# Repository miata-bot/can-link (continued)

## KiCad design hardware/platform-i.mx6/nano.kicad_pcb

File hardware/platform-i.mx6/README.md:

# I.MX6 Platform Board

This is where the functioning I.MX6 board will go when it's done.
Currently in production at PCBWay, assuming the devboard works, this project will get reworked into the correct form factor for the Platform board. It's already the correct width, just needs tidying and connectors.

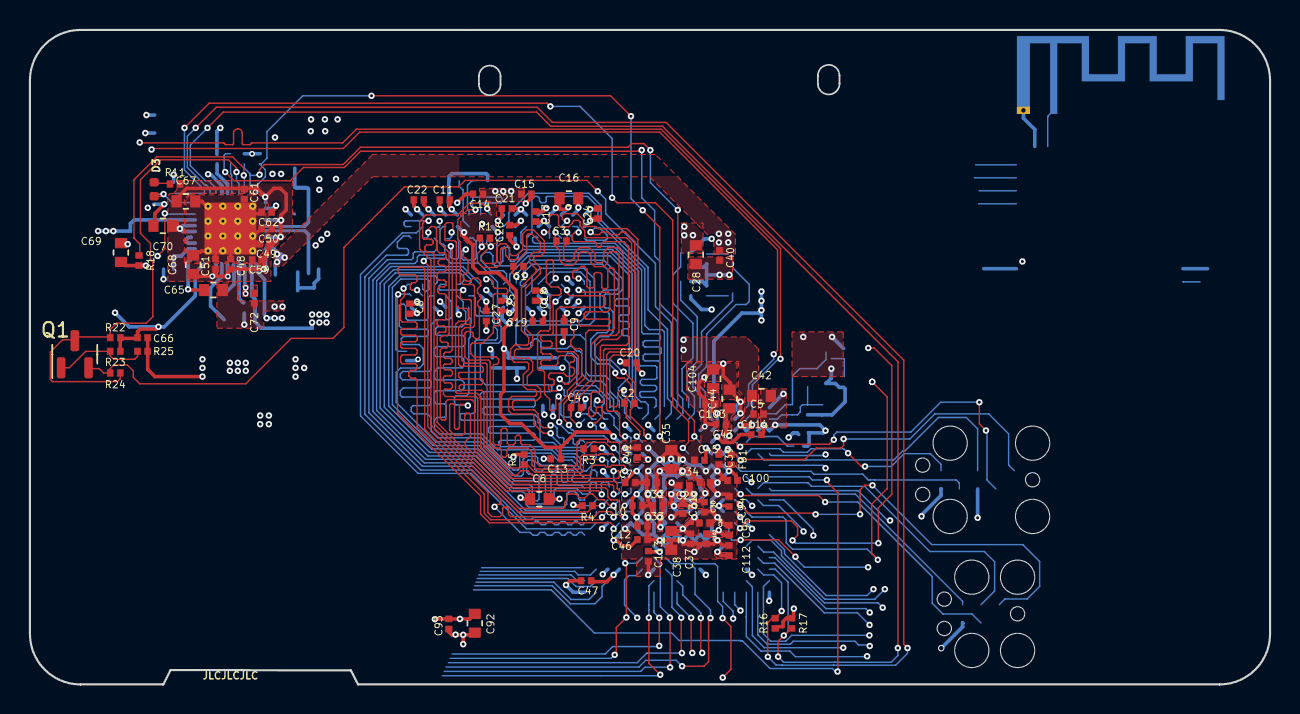
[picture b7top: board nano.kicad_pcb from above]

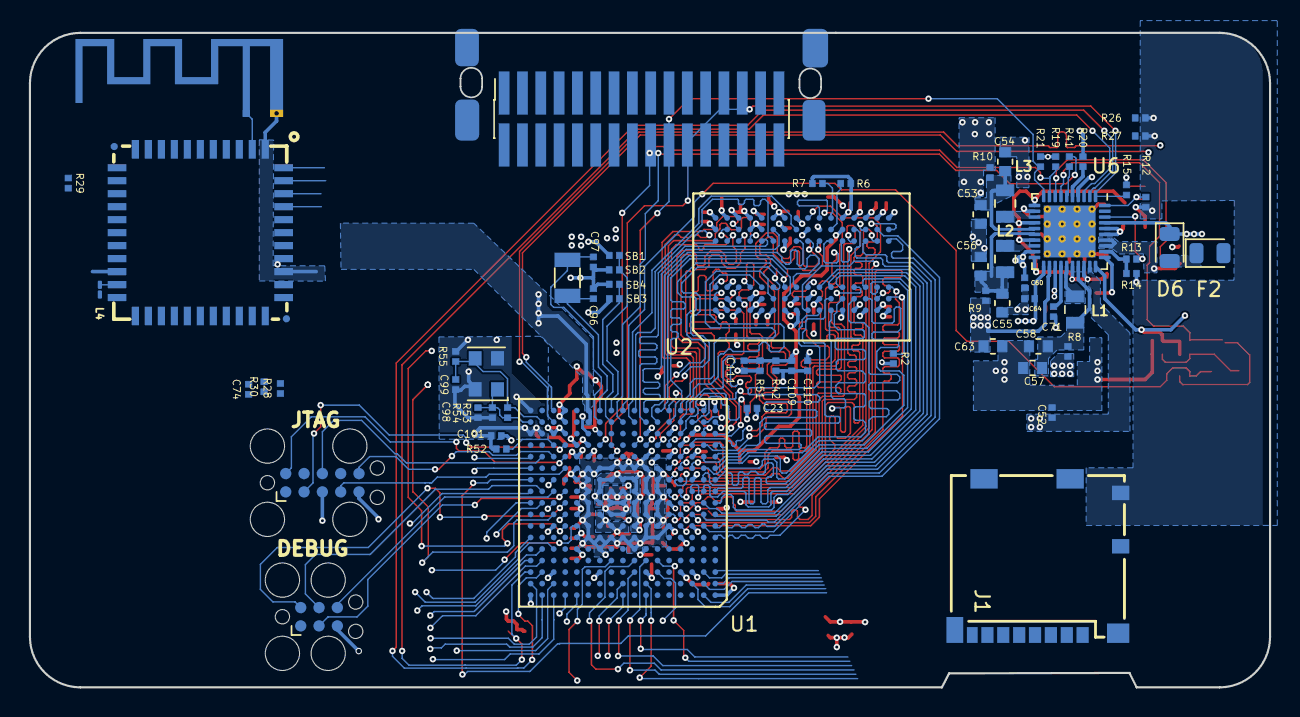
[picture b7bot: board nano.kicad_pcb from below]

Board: 4 copper layers, 86.0 x 45.4 mm, 153 parts (67 on the bottom side), 141 nets.

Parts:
ANT1: PCB_ANTENNA; Texas_SWRA117D_2.4GHz_Left
C1, C2, C3, C4: 2.2pF; C_0402_narrow
C5, C7, C8, C9, C10, C11, C12, C13, C14, C15, C17, C18, C19, C20, C21, C22, C23, C24, C25, C26, C27, C30, C31, C32, C33, C34, C36, C37, C40, C41, C43, C45, C46, C47, C94, C95, C102, C114: 0.22uF; C_0402_narrow
C6, C42, C44, C53, C54, C55, C56, C57, C58, C104: 10uF; C_0603_narrow
C16, C28, C35, C38, C92: 22uF; C_0603_narrow
C29, C39, C48, C49, C50, C52, C60, C62, C110: 4.7uF; C_0402_narrow
C51, C59, C61, C64, C71, C72, C101: 1uF; C_0402_narrow
C63: 1uF; C_0603_narrow
C65: 0.1uF; C_0603_narrow
C66: 0.47uF; C_0402_narrow
C67, C68: 100uF; C_0603_narrow
C69, C70: 4.7uF; C_0603_narrow
C74: 4.7F; C_0402_narrow
C93, C100, C103, C109, C111, C112, C113: 0.1uF; C_0402_narrow
C96, C97, C98, C99: 18pF; C_0402_narrow
D3: LED; LED_0402_1005Metric
D6: D_Schottky; D_0805_2012Metric
F2: Polyfuse; D_0805_2012Metric
FB1: Bead; R_0402_narrow
J1: SD-104031; uSD_104031
J2: TAG_CONNECT_JTAG; Tag-Connect_TC2050-IDC-FP_2x05_P1.27mm_Vertical
J2#2: Conn_02x15_Odd_Even_Shielded; PinSocket_2x16_P1.27mm_Vertical_SMD
J3: TC2030-IDC; Tag-Connect_TC2030-IDC-FP_2x03_P1.27mm_Vertical
L1, L2, L3: 1uH; L_0805_narrow
L4: 3.3uH; L_01005_0402Metric_Pad0.57x0.30mm_HandSolder
MOD1: RTL8723BS; RL-SM02BD(RTL8723BS)
Q1: 2SK3018; SOT-23
R1: 470; R_0402_narrow
R2, R4, R5: 10K; R_0402_narrow
R3, R6, R7: 240; R_0402_narrow
R8, R9, R10: 0.02; R_0402_narrow
R11: 47; R_0402_narrow
R12, R14, R24: DNP; R_0402_narrow
R13, R16, R17, R52: 4.7K; R_0402_narrow
R15, R18, R19, R21, R22, R23, R25: 100K; R_0402_narrow
R20, R41: 0R; R_0402_narrow
R26, R27: 5.1k; R_0402_narrow
R28, R29: 1k; R_0402_narrow
R30: 7.13; R_0402_narrow
R42, R51: 1.5K; R_0402_narrow
R53: 1M; R_0402_narrow
R54: 499; R_0402_narrow
R55: 2.2M; R_0402_narrow
SB1, SB2, SB3, SB4: 4.7K; R_0402_narrow
U1: IMX6UL_BGA289
U2: DDR3_BGA96
U6: PF1550; QFN-40-1EP_5x5mm_P0.4mm_EP3.6x3.6mm_ThermalVias
XTAL2: 24MHz 50ppm; Oscillator_SMD_EuroQuartz_XO32-4Pin_3.2x2.5mm
Y1: 32.768 kHz; Crystal_SMD_3215-2Pin_3.2x1.5mm

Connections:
5V: D6.1 (K), U1.T12 (USB_OTG1_VBUS), U1.U12 (USB_OTG2_VBUS), U6.37 (VBUSIN(VIN))
/Clock_and_Control/BOOT0: SB3.1, SB4.1, U1.T10 (BOOT_MODE0)
/Clock_and_Control/BOOT1: SB1.1, SB2.1, U1.U10 (BOOT_MODE1)
/Clock_and_Control/IMX_XTALI: C99.1, R53.1, R55.1, U1.T16 (XTALI), XTAL2.3
/Clock_and_Control/IMX_XTALO: C98.1, R53.2, R54.1, U1.T17 (XTALO), XTAL2.1
/Clock_and_Control/JTAG_MOD: R52.2, U1.P15 (JTAG_MOD)
/Clock_and_Control/JTAG_TCK: J2.4 (SWDCLK/TCK), U1.M14 (JTAG_TCK)
/Clock_and_Control/JTAG_TDI: J2.8 (NC/TDI), U1.N16 (JTAG_TDI)
/Clock_and_Control/JTAG_TDO: J2.6 (SWO/TDO), U1.N15 (JTAG_TDO)
/Clock_and_Control/JTAG_TMS: J2.2 (SWDIO/TMS), U1.P14 (JTAG_TMS)
/Clock_and_Control/JTAG_TRST_B: J2.10 (~RESET), U1.N14 (JTAG_TRST_B)
/Clock_and_Control/RTC_XTALI: C97.1, U1.T11 (RTC_XTALI), Y1.2
/Clock_and_Control/RTC_XTALO: C96.1, U1.U11 (RTC_XTALO), Y1.1
/Clock_and_Control/VDDA_ADC: C100.1, C101.1, FB1.2, U1.L13 (VDDA_ADC_3P3), U1.M13 (ADC_VREFH)
/DDR/A0: U1.L5 (DRAM_ADDR00), U2.N3 (A0)
/DDR/A1: U1.H2 (DRAM_ADDR01), U2.P7 (A1)
/DDR/A2: U1.K1 (DRAM_ADDR02), U2.P3 (A2)
/DDR/A3: U1.M2 (DRAM_ADDR03), U2.N2 (A3)
/DDR/A4: U1.K4 (DRAM_ADDR04), U2.P8 (A4)
/DDR/A5: U1.L1 (DRAM_ADDR05), U2.P2 (A5)
/DDR/A6: U1.G2 (DRAM_ADDR06), U2.R8 (A6)
/DDR/A7: U1.H4 (DRAM_ADDR07), U2.R2 (A7)
/DDR/A8: U1.J4 (DRAM_ADDR08), U2.T8 (A8)
/DDR/A9: U1.L2 (DRAM_ADDR09), U2.R3 (A9)
/DDR/A10: U1.M4 (DRAM_ADDR10), U2.L7 (A10_AP)
/DDR/A11: U1.K3 (DRAM_ADDR11), U2.R7 (A11)
/DDR/A12: U1.L4 (DRAM_ADDR12), U2.N7 (A12_BC#)
/DDR/A13: U1.H3 (DRAM_ADDR13), U2.T3 (A13)
/DDR/A14: U1.G1 (DRAM_ADDR14), U2.T7 (A14)
/DDR/A15: U1.K5 (DRAM_ADDR15), U2.M7 (A15)
/DDR/BA0: U1.M1 (DRAM_SDBA0), U2.M2 (BA0)
/DDR/BA1: U1.H1 (DRAM_SDBA1), U2.N8 (BA1)
/DDR/BA2: U1.K2 (DRAM_SDBA2), U2.M3 (BA2)
/DDR/CAS#: U1.J2 (DRAM_CAS_B), U2.K3 (CAS#)
/DDR/CK+: R1.2, U1.P1 (DRAM_SDCLK0_P), U2.J7 (CK)
/DDR/CK-: R1.1, U1.P2 (DRAM_SDCLK0_N), U2.K7 (CK#)
/DDR/CKE0: R5.1, U1.M3 (DRAM_SDCKE0), U2.K9 (CKE)
/DDR/CKE1: R4.1, U1.J3 (DRAM_SDCKE1), U2.J9 (CKE1)
/DDR/CS0#: U1.N2 (DRAM_CS0_B), U2.L2 (CS#)
/DDR/CS1#: U1.H5 (DRAM_CS1_B), U2.L1 (CS1)
/DDR/DML: U1.T7 (DRAM_DQM0), U2.E7 (DML)
/DDR/DMU: U1.T3 (DRAM_DQM1), U2.D3 (DMU)
/DDR/DQL0: U1.T4 (DRAM_DATA00), U2.E3 (DQL0)
/DDR/DQL1: U1.U6 (DRAM_DATA01), U2.H3 (DQL4)
/DDR/DQL2: U1.T6 (DRAM_DATA02), U2.H7 (DQL7)
/DDR/DQL3: U1.U7 (DRAM_DATA03), U2.F8 (DQL3)
/DDR/DQL4: U1.U8 (DRAM_DATA04), U2.F7 (DQL1)
/DDR/DQL5: U1.T8 (DRAM_DATA05), U2.H8 (DQL5)
/DDR/DQL6: U1.T5 (DRAM_DATA06), U2.G2 (DQL6)
/DDR/DQL7: U1.U4 (DRAM_DATA07), U2.F2 (DQL2)
/DDR/DQSL+: C1.1, C2.1, U1.P6 (DRAM_SDQS0_P), U2.F3 (DQSL)
/DDR/DQSL-: C1.2, C2.2, U1.P7 (DRAM_SDQS0_N), U2.G3 (DQSL#)
/DDR/DQSU+: C3.1, C4.1, U1.T1 (DRAM_SDQS1_P), U2.C7 (DQSU)
/DDR/DQSU-: C3.2, C4.2, U1.T2 (DRAM_SDQS1_N), U2.B7 (DQSU#)
/DDR/DQU0: U1.U2 (DRAM_DATA08), U2.D7 (DQU0)
/DDR/DQU1: U1.U3 (DRAM_DATA09), U2.C3 (DQU1)
/DDR/DQU2: U1.U5 (DRAM_DATA10), U2.C8 (DQU2)
/DDR/DQU3: U1.R4 (DRAM_DATA11), U2.C2 (DQU3)
/DDR/DQU4: U1.P5 (DRAM_DATA12), U2.A7 (DQU4)
/DDR/DQU5: U1.P3 (DRAM_DATA13), U2.A2 (DQU5)
/DDR/DQU6: U1.R2 (DRAM_DATA14), U2.B8 (DQU6)
/DDR/DQU7: U1.R1 (DRAM_DATA15), U2.A3 (DQU7)
/DDR/ODT0: U1.N1 (DRAM_ODT0), U2.K1 (ODT)
/DDR/ODT1: U1.F1 (DRAM_ODT1), U2.J1 (ODT1)
/DDR/RAS#: U1.M5 (DRAM_RAS_B), U2.J3 (RAS#)
/DDR/RESET#: R2.1, U1.G4 (DRAM_RESET), U2.T2 (RESET#)
/DDR/WE#: U1.J1 (DRAM_SDWE_B), U2.L3 (WE#)
/DDR/ZQ: R6.2, U2.L8 (ZQ)
/DDR/ZQ1: R7.2, U2.L9 (ZQ1)
/DDR/ZQPAD: R3.2, U1.N4 (DRAM_ZQPAD)
/IMX_Peripherals_2/VDDUSB_CAP: C103.1, C104.1, U1.R12 (VDD_USB_CAP)
/IMX_Power_Pins/VDD_SNVS_CAP: C45.1, U1.N12 (VDD_SNVS_CAP)
/PMIC PF1550/CHGB: D3.1 (K), R12.1, U6.40 ((GND)CHGB)
/PMIC PF1550/ON_KEY: R18.1, U6.8 (ONKEY)
/PMIC PF1550/POWERON: R41.1, U6.6 (POWERON)
/PMIC PF1550/STANDBY: Q1.3 (D), R22.2, R24.1, U6.7 (STANDBY)
/PMIC PF1550/SW1LX: L1.2, U6.25 (SW1LX)
/PMIC PF1550/SW1OUT: C57.1, C58.1, L1.1, R8.1, U6.27 (SW1FB)
/PMIC PF1550/SW2LX: L2.2, U6.18 (SW2LX)
/PMIC PF1550/SW2OUT: C55.1, C56.1, L2.1, R9.1, U6.16 (SW2FB)
/PMIC PF1550/SW3LX: L3.2, U6.13 (SW3LX)
/PMIC PF1550/SW3OUT: C53.1, C54.1, L3.1, R10.1, U6.15 (SW3FB)
/PMIC PF1550/VCORE: C71.1, U6.24 (VCORE)
/PMIC PF1550/VDDOTP: R20.2, U6.5 (VDDOTP)
/PMIC PF1550/VDIG: C72.1, U6.23 (VDIG)
/WIFI_BT/SDIO_VSEL: MOD1.29, R30.2
/WIFI_BT/VIN_LDO: C74.1, L4.2, MOD1.23
/WIFI_BT/VIN_LDO_OUT: L4.1, MOD1.21
BATT_THM: R13.1, R14.2, U6.32 (THM(GND))
BOARD_SCL: R17.2, U1.C17 (ENET2_RX_DATA0), U6.3 (SCL)
BOARD_SDA: R16.2, U1.C16 (ENET2_RX_DATA1), U6.2 (SDA)
BT_RST: MOD1.34, R28.2, U1.N17 (GPIO1_IO08)
BT_WAKE: MOD1.6, U1.M17 (GPIO1_IO05)
DBG_CTS: J3.2, U1.J14 (UART1_RTS_B)
DBG_GPIO0: MOD1.12, R29.2, U1.L15 (GPIO1_IO01)
DBG_RTS: J3.6, U1.K15 (UART1_CTS_B)
DBG_RXD: J3.3, U1.K14 (UART1_TX_DATA)
DBG_TXD: J3.4, U1.K16 (UART1_RX_DATA)
DCDC_3V3: C92.1, C93.1, C94.1, C95.1, C102.1, C112.1, C113.1, J1.4 (VDD), MOD1.9, MOD1.22, R10.2, R15.1, R16.1, R17.1, R28.1, R29.1, U1.E7 (NVCC_NAND), U1.E13 (NVCC_LCD), U1.F13 (NVCC_ENET), U1.H13 (NVCC_UART), U1.J13 (NVCC_GPIO), U6.4 (VDDIO)
DRAM_1V35: C6.1, C7.1, C8.1, C9.1, C10.1, C11.1, C12.1, C16.1, C17.1, C18.1, C19.1, C20.1, C21.1, C22.1, C23.1, C24.1, C25.1, C26.1, C27.1, C63.1, C109.1, C110.1, R9.2, R42.2, U1.G6 (NVCC_DRAM), U1.H6 (NVCC_DRAM), U1.J6 (NVCC_DRAM), U1.K6 (NVCC_DRAM), U1.L6 (NVCC_DRAM), U1.M6 (NVCC_DRAM), U2.A1 (VDDQ), U2.A8 (VDDQ), U2.B2 (VDD), U2.C1 (VDDQ), U2.C9 (VDDQ), U2.D2 (VDDQ), U2.D9 (VDD), U2.E9 (VDDQ), U2.F1 (VDDQ), U2.G7 (VDD), U2.H2 (VDDQ), U2.H9 (VDDQ), U2.K2 (VDD), U2.K8 (VDD), U2.N1 (VDD), U2.N9 (VDD), U2.R1 (VDD), U2.R9 (VDD), U6.22 (VINREFDDR)
GND: ANT1.2 (Shield), C5.2, C6.2, C7.2, C8.2, C9.2, C10.2, C11.2, C12.2, C13.2, C14.2, C15.2, C16.2, C17.2, C18.2, C19.2, C20.2, C21.2, C22.2, C23.2, C24.2, C25.2, C26.2, C27.2, C28.2, C29.2, C30.2, C31.2, C32.2, C33.2, C34.2, C35.2, C36.2, C37.2, C38.2, C39.2, C40.2, C41.2, C42.2, C43.2, C44.2, C45.2, C46.2, C47.2, C48.2, C49.2, C50.2, C51.2, C52.2, C53.2, C54.2, C55.2, C56.2, C57.2, C58.2, C59.2, C60.2, C61.2, C62.2, C63.2, C64.2, C65.2, C66.2, C67.2, C68.2, C69.2, C70.2, C71.2, C72.2, C74.2, C92.2, C93.2, C94.2, C95.2, C96.2, C97.2, C98.2, C99.2, C100.2, C101.2, C102.2, C103.2, C104.2, C110.2, C111.2, C112.2, C113.2, C114.2, J1.6 (GND), J1.10 (SW2), J1.11 (Shield1), J1.12 (Shield2), J1.13 (Shield3), J1.14 (Shield4), J2.3 (GND), J2.5 (GND), J2#2.14, J2#2.16, J2#2.18, J3.5, MOD1.1, MOD1.20, MOD1.31, MOD1.33, MOD1.36, R2.2, R3.1, R4.2, R5.2, R6.1, R7.1, R12.2, R14.1, R20.1, R25.1, R26.2, R27.2, R30.1, R51.1, R52.1, R54.2, R55.2, SB2.2, SB4.2, U1.A1 (VSS), U1.A17 (VSS), U1.C3 (VSS), U1.C7 (VSS), U1.C11 (VSS), U1.C15 (VSS), U1.E8 (VSS), U1.E11 (VSS), U1.F6 (VSS), U1.F7 (VSS), U1.F8 (VSS), U1.F9 (VSS), U1.F10 (VSS), U1.F11 (VSS), U1.F12 (VSS), U1.G3 (VSS), U1.G5 (VSS), U1.G7 (VSS), U1.G12 (VSS), U1.G15 (VSS), U1.H7 (VSS), U1.H12 (VSS), U1.J5 (VSS), U1.J7 (VSS), U1.J12 (VSS), U1.K7 (VSS), U1.K12 (VSS), U1.L3 (VSS), U1.L7 (VSS), U1.L12 (VSS), U1.M7 (VSS), U1.M8 (VSS), U1.M9 (VSS), U1.M10 (VSS), U1.M11 (VSS), U1.M12 (NGND_KEL0), U1.N3 (VSS), U1.N5 (VSS), U1.N7 (TEST_MODE), U1.R3 (VSS), U1.R5 (VSS), U1.R7 (VSS), U1.R11 (VSS), U1.R16 (VSS), U1.R17 (VSS), U1.T14 (VSS), U1.U1 (VSS), U1.U14 (VSS), U1.U17 (VSS), U2.A9 (VSS), U2.B1 (VSSQ), U2.B3 (VSS), U2.B9 (VSSQ), U2.D1 (VSSQ), U2.D8 (VSSQ), U2.E1 (VSS), U2.E2 (VSSQ), U2.E8 (VSSQ), U2.F9 (VSSQ), U2.G1 (VSSQ), U2.G8 (VSS), U2.G9 (VSSQ), U2.J2 (VSS), U2.J8 (VSS), U2.M1 (VSS), U2.M9 (VSS), U2.P1 (VSS), U2.P9 (VSS), U2.T1 (VSS), U2.T9 (VSS), U6.41 (EP), XTAL2.2, XTAL2.4
LICELL: C65.1, U6.31 (LICELL)
NVCC_CSI: C46.1, C52.1, U1.F4 (NVCC_CSI), U6.29 (VLDO1)
NVCC_PLL_OUT: C43.1, C44.1, U1.P13 (NVCC_PLL)
NVCC_SD: C47.1, C62.1, U1.C4 (NVCC_SD1), U6.12 (VLDO3)
unnamed: ANT1.1 (A), MOD1.2
unnamed: D3.2 (A), R11.1
unnamed: D6.2 (A), F2.1
unnamed: Q1.1 (G), R23.2, R25.2
unnamed: R13.2, U6.38 (INT2P7(LDO2P7))
PMIC_INT: R19.1, U1.P11 (SNVS_TAMPER2), U6.9 (INTB)
PMIC_ON_REQ: R41.2, U1.T9 (SNVS_PMIC_ON_REQ)
PMIC_STBY_REQ: Q1.2 (S), R24.2, U1.U9 (CCM_PMIC_STBY_REQ)
PMIC_WDI: R15.2, U1.N10 (SNVS_TAMPER7), U6.1 (WDI)
POR_B: R21.1, U1.P8 (POR_B), U6.10 (RESETBMCU)
SD1_CD_B: J1.9 (SW1), U1.L17 (GPIO1_IO03)
SD1_CLK: J1.5 (CLK), U1.C1 (SD1_CLK)
SD1_CMD: J1.3 (CMD), U1.C2 (SD1_CMD)
SD1_D0: J1.7 (D0), U1.B3 (SD1_DATA0)
SD1_D1: J1.8 (D1), U1.B2 (SD1_DATA1)
SD1_D2: J1.1 (D2), U1.B1 (SD1_DATA2)
SD1_D3: J1.2 (D3), U1.A2 (SD1_DATA3)
SDHC_CLK: MOD1.17, U1.D8 (NAND_RE_B)
SDHC_CMD: MOD1.16, U1.C8 (NAND_WE_B)
SDHC_DATA0: MOD1.18, U1.D7 (NAND_DATA00)
SDHC_DATA1: MOD1.19, U1.B7 (NAND_DATA01)
SDHC_DATA2: MOD1.14, U1.A7 (NAND_DATA02)
SDHC_DATA3: MOD1.15, U1.D6 (NAND_DATA03)
UART2_CTS: MOD1.41, U1.J15 (UART2_CTS_B)
UART2_RTS: MOD1.44, U1.H14 (UART2_RTS_B)
UART2_RXD: MOD1.42, U1.J16 (UART2_RX_DATA)
UART2_TXD: MOD1.43, U1.J17 (UART2_TX_DATA)
VBATT: C69.1, R18.2, U6.33 ((NC)VBATT1), U6.34 ((NC)VBATT2)
VDD_ARM_CAP: C36.1, C37.1, C38.1, U1.G9 (VDD_ARM_CAP), U1.G10 (VDD_ARM_CAP), U1.G11 (VDD_ARM_CAP), U1.H11 (VDD_ARM_CAP)
VDD_HIGH_CAP: C5.1, C41.1, C42.1, U1.N6 (NVCC_DRAM_2P5), U1.R14 (VDD_HIGH_CAP), U1.R15 (VDD_HIGH_CAP)
VDD_HIGH_IN: C39.1, C40.1, C60.1, FB1.1, U1.N13 (VDD_HIGH_IN), U6.19 (VLDO2)
VDD_SNVS: C66.1, C114.1, R19.2, R21.2, R22.1, R23.1, SB1.2, SB3.2, U1.P12 (VDD_SNVS_IN), U6.30 (VSNVS)
VDD_SOC_CAP: C32.1, C33.1, C34.1, C35.1, U1.G8 (VDD_SOC_CAP), U1.H8 (VDD_SOC_CAP), U1.J8 (VDD_SOC_CAP), U1.J11 (VDD_SOC_CAP), U1.K8 (VDD_SOC_CAP), U1.K11 (VDD_SOC_CAP), U1.L8 (VDD_SOC_CAP), U1.L9 (VDD_SOC_CAP), U1.L10 (VDD_SOC_CAP), U1.L11 (VDD_SOC_CAP)
VDD_SOC_IN: C28.1, C29.1, C30.1, C31.1, R8.2, U1.H9 (VDD_SOC_IN), U1.H10 (VDD_SOC_IN), U1.J9 (VDD_SOC_IN), U1.J10 (VDD_SOC_IN), U1.K9 (VDD_SOC_IN), U1.K10 (VDD_SOC_IN)
VREFDDR: C13.1, C14.1, C15.1, C64.1, C109.2, C111.1, R42.1, R51.2, U1.P4 (DRAM_VREF), U2.H1 (VREFDQ), U2.M8 (VREFCA), U6.21 (VREFDDR)
VSYS: C48.1, C49.1, C50.1, C51.1, C59.1, C61.1, C67.1, C68.1, C70.1, R11.2, U6.11 (VLDO3IN), U6.14 (SW3IN), U6.17 (SW2IN), U6.20 (VLDO2IN), U6.26 (SW1IN), U6.28 (VLDO1IN), U6.35 (VSYS1), U6.36 (VSYS2)

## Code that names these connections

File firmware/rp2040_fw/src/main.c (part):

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#define RGB0_G_PIN 27
#define RGB0_B_PIN 26

#define RGB1_R_PIN 25
#define RGB1_G_PIN 24
#define RGB1_B_PIN 23

#define WS2812_PIN 4

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    PICO_LOGI("initialize rgb1");

    RGB_t rgb1 = {
        .gpio_r = RGB1_R_PIN,
        .gpio_g = RGB1_G_PIN,
        .gpio_b = RGB1_B_PIN,
        .r = 0,
        .g = 0,
        .b = 0,
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
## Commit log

2022-02-21 Add macbook sshkey
2022-02-21 Add can library fork
2022-03-14 Add parser for haltech CAN data
2022-03-17 first test w/ haltech!!!
2022-03-17 Rename project
2022-03-17 Initial commit for scripting engine
2022-03-17 Missed rename
2022-03-18 Add radio
2022-03-18 asdf
2022-03-18 Radio poc, canscript integration
2022-03-22 Radio
2022-03-22 GPS!
2022-03-23 test app
2022-03-23 uknowhowitgoes
2022-03-23 POC Works!
2022-03-24 Add PWM
2022-03-24 Add RGB LED instead of external controller
2022-03-24 Misc cleanup
2022-03-25 Gadget
2022-03-28 idr what this is
2022-03-28 Add first rev of schematic. Needs cleanup
2022-03-28 Schematic Progress
    Almost done. Need to add the PWM signals and do the packet radio and GPS
2022-03-30 Layout almost done...
2022-03-31 uknow
2022-03-31 Start layout
2022-04-01 fanout is hard
2022-04-01 Nearly done!
2022-04-01 Add logos
2022-04-02 Add README.md and Requirements.md
2022-04-03 Add more gadget stuff
2022-04-03 Add IIO port
2022-04-03 Rename CAN library
2022-04-06 sadg
2022-04-07 routingm progress 2
2022-04-07 Almost done
2022-04-07 Fix DRC errors
2022-04-07 Step away from the computer
2022-04-08 Submitted for fab
2022-04-08 Remove BSS1338
2022-04-11 i hate myself
2022-04-11 what am i even doing
2022-04-12 Can't change it now!
2022-04-12 Schematic cleanup
2022-04-12 Hardware v2 Rev A Release
2022-04-20 start imx board
2022-04-20 redesign into a "carrier" type setup
2022-04-21 backup
2022-04-22 almost Finish carrier board
2022-04-22 Carrier submitted to assembly
2022-04-24 Add 3v3 regulator for carrier board
2022-04-25 Add motor controller for popups or whatever
2022-04-25 Finish motor driver
2022-04-25 Finish motor controller
2022-04-25 ughhhhhhhhhhhhhhhhhhhhhhh
2022-04-26 misc tweaks
2022-04-26 Submitted for fab.
    Future cone, could u squash the last few commits and tag this as a
    release
2022-04-27 Update docs
2022-04-27 Add TODOs
2022-04-27 Start reworking imx board into the new form factor
2022-04-27 haltech <-> na6 adapter
2022-04-28 Finish Haltech adapter
2022-04-28 Well that doesn't fit lol
2022-04-28 CM4 platform board outline
2022-04-29 circle pcb go brrrr lmao
2022-04-29 ?remind 2 hours to route the screen next
2022-04-30 fdsa
2022-05-01 route diff pairs or whatever idr
2022-05-01 tune length of spi signal
2022-05-01 Guess it's done
2022-05-03 :ha:
2022-05-03 im cry
2022-05-06 im the worst
2022-05-06 Compromises were made
2022-05-07 restart esp gauge
2022-05-08 Remove submodules
2022-05-09 Add RP2040 Firmware prototype
2022-05-09 esp firmware scafolding
2022-05-10 Add pullups to sdcard
2022-05-10 Add ability to load lua scripts from SDCard
2022-05-10 Fix antenna impedance
2022-05-10 add debug headers, change pmic to something in stock
2022-05-10 Ble scafolding
2022-05-11 Sort esp firmware into more files
2022-05-12 restart gauge pcb
2022-05-13 cauge design progress
2022-05-13 Update PCBs to share the same components
    * 3x flash memory
    * CAN transciever
2022-05-13 Update images and project names
2022-05-15 Calculate initial values for antenna resistor matching network
2022-05-15 Calculate clock values
2022-05-15 start filling out BOM
2022-05-16 Fill out BOM for mouser
2022-05-18 gerbertiem
2022-05-18 bom bom bom bom
2022-05-18 Submit for fab. tagme
2022-05-23 Initial scafolding of sx1231 driver.
2022-05-24 radio almost works acking still busted
2022-05-28 hardware updates: fix SPI bus on pico and flatten radio module
2022-05-28 debug deez
2022-05-28 start to break into sheets
2022-05-29 first test!~!!
2022-05-29 implement RPC between pico and esp32
2022-05-29 Bluetooth works
2022-05-30 Flush out motor driver mostly
    also adds a really useful console
2022-05-31 pcb updates
2022-05-31 devboard or something idk
2022-06-01 i can't believe what they did to my boy
2022-06-02 urmom
2022-06-02 updates nearly complete
2022-06-03 add USB VIN
2022-06-03 add motor controller board
2022-06-03 Finish routing motor controller board
2022-06-03 start bringup of USB iface
2022-06-03 Add ini config system
2022-06-05 Implement USB mass storage endpoint
2022-06-05 astyle sources
2022-06-05 hopefully restore usb serial console
2022-06-05 remove endless loop lol
2022-06-06 more cleanup, gonna write lua drivers next
2022-06-06 pico sync and lua driver
2022-06-06 implement some radio stuff
2022-06-07 add WIP analog/digital input expander
2022-06-08 god i wish i remembered what this was
2022-06-08 u like resistors
2022-06-08 finished i guess
2022-06-08 panelize i guess idk
2022-06-09 antenna
2022-06-10 replace pmic
2022-06-10 iasdf
2022-06-11 schematic rework progress
2022-06-11 schematic almost done
2022-06-11 almost done picking components i think
2022-06-11 fix main sheet grid
2022-06-11 muh colored schematics
2022-06-12 antenna af
2022-06-13 pizz
2022-06-13 im a piece of garbage
2022-06-14 aaaaa
2022-06-14 AAAAAAA
2022-06-14 aaaaaaaaaaa
2022-06-14 missed pcb layout ig?
2022-06-15 routing nearly done.
2022-06-22 why am i doing this
2022-06-22 add analog input filtering and protection
2022-06-28 Update docs and TODOS
    Add TODOs
2022-06-28 CM4 Prototype
2022-06-28 ESP Multi Gauge prototype
2022-06-28 Multi gauge pcb design
2022-06-28 Radio hardware and software design
2022-06-28 Prototype motor controller device
2022-06-28 Prototype analog/digital input expander
2022-06-28 Bom fillout + wiring
2022-06-28 firmware for neopixel testing
2022-06-28 hw updates based on prototype issues
    * Removes unused hardware and firmware projectes
    * Adds some documentation and bom
    * cleanup READMEs
2022-06-28 Hardware updates
    * fix messed up +12v pin
    * add a ground output for neopixels on both channels
    * add a i2c microphone
    * clean up schematic
    * calculate component values for the LED drivers
2022-06-29 wtf am i even doing lmfao
2022-07-01 Add sqlite database for configuring the device
2022-07-01 hardware updates from board bringup
2022-07-01 Layout updates
2022-07-01 V5 Rev B Hardware release
2022-07-04 implement register-based VM and assembler
2022-07-04 add more accurate time source
2022-07-05 app pt 2 s
2022-07-05 it works
2022-07-06 attempt to cleanup bluetooth
2022-07-06 more bleeeeeeeeeeeeeeeeee
2022-07-06 oops cooked a board
2022-07-07 can you imagine if i committed my discord token
2022-07-08 hyonk
2022-07-08 Add FET drivers
2022-07-08 rainbow pattern
2022-07-09 Add docs for CAN data formt
2022-07-09 Start multi-gauge again
2022-07-09 Add APP assets for android APK
2022-07-10 start integrating firmware
2022-07-11 more firmware shit
2022-07-11 Compiles now
2022-07-11 Sqlite3 interface works
2022-07-11 rename sqlite3 context
2022-07-13 hw updates based on latest boards
2022-07-13 Board bringup complete, move to real firmware
2022-07-14 im suck
2022-07-14 hrggghhhhhhh
2022-07-14 Implement loading all data from the DB
2022-07-14 implement saving/loading private data for each mode
2022-07-14 ughhhhhhhh
2022-07-14 fixed that
2022-07-14 Implement static color change
2022-07-15 implement solid color change pt 2
2022-07-15 time for cleanup
2022-07-15 flip rainbow pattern diretion
2022-07-16 https://www.youtube.com/watch?v=FZUcpVmEHuk&ab_channel=billwurtz
2022-07-17 implement config endpoint for ble
2022-07-17 almost done integrating radio
2022-07-17 radio compiles, time for testing
2022-07-17 Radio works!!
2022-07-18 this probably does not work
2022-07-18 raaaaadioooooooooooo
2022-07-18 Fix radio compile errors
2022-07-18 (hopefully) implement leadership discovery
2022-07-18 cloc
2022-07-19 OTA via BT. This is not viable, delete
2022-07-19 USB bringup
2022-07-19 more usb testing
2022-07-19 more usb updates
2022-07-19 asdfasdfasdf
2022-07-20 this is the firmware that is on Easyy's and Jake's device
2022-07-22 Update installation diagram
2022-07-24 ctrl+c, ctrl+v
2022-07-26 Implement PWM RGB control
2022-07-31 Hardware updates, firmware updates blah blah blah
2022-07-31 Add patch to sqlite3 to fix build
2022-08-01 implement pulse mode and chase mode
2022-08-09 hardware updates
2022-08-10 3am matg computer touching, fixed all the things hopefully
2022-08-10 more hardware updates. need to sort out the antenna for the radio next
2022-08-11 ughughughugh
2022-08-11 hw updates pt 69 thousand
2022-08-24 Update to latest IDF
2022-08-24 Update to latest idf lib
2022-08-26 Scafold V2 Framework
    This refactors a lot of documentation and shell/support code to
    implement a new core of the underglow controller device
2022-08-26 Fix sqlite3 commit hash
2022-08-27 more docs
2022-08-27 Docs
2022-10-18 hopefully this isn't important
2022-11-13 Provision: Add small native app for device provisioning and tuning
2022-11-13 provision: implement script editor persistence into DB
2022-11-14 provision: add check for pending edits before quitting
2022-11-14 provision: add windows build
2022-11-14 provision: add version information
2022-11-14 provision: add about and license modals
2022-11-14 provision: build: build x86 exe in release mode
2022-11-14 provision: add emscripten platform
2022-11-14 firmware: fix build on latest idf lib
2022-11-14 firmware: remove extra modules
2022-11-14 firmware: companion: remove old implementations
2022-11-15 provision: sqlite: ignore dirty submodule
2022-11-15 hardware: prepare for production run
2022-11-15 hardware: select some JLCPCB components
2022-11-16 jlc: add throwaway project for searching for parts
2022-11-17 hardware: assign more JLC parts
2022-11-17 fix hole locations
2022-11-17 update hole footprints and final hole location
2022-11-29 add case models
2022-12-01 hardware: add teardrops to vias
2023-03-21 add mounting and antenna holes to case
